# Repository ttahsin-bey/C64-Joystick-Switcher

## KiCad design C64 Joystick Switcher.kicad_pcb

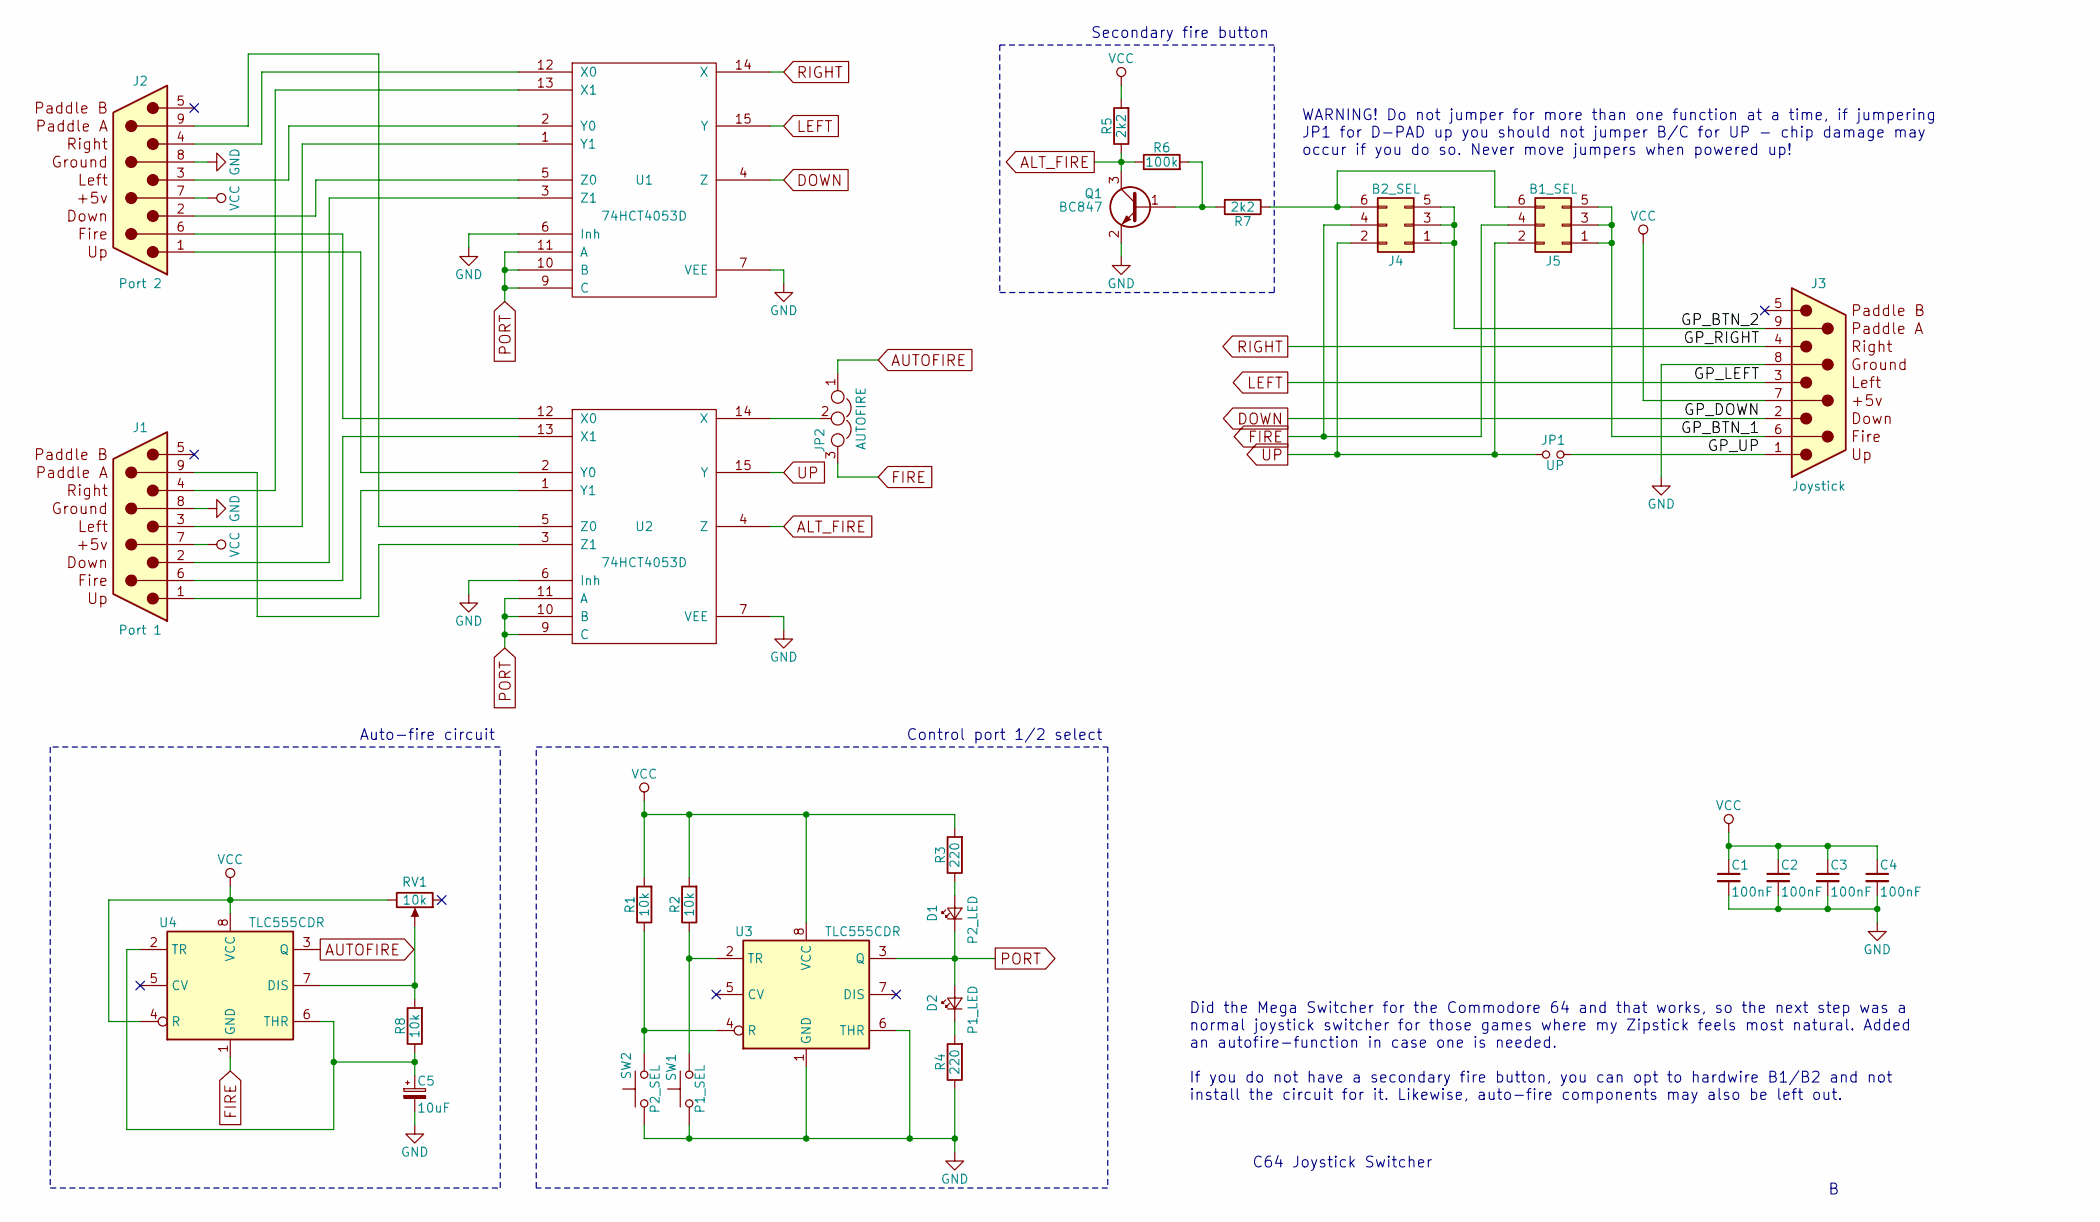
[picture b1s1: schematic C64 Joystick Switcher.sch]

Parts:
C1, C2, C3, C4: 100nF; C_0603_1608Metric; JLCPCB C14663
C5: 10uF; CP_EIA-3216-18_Kemet-A; JLCPCB C7171
D1: P2_LED; LED_0603_1608Metric; JLCPCB C2286
D2: P1_LED; LED_0603_1608Metric; JLCPCB C2286
J1: Port 1; DSUB-9_Female_Horizontal_P2.77x2.84mm_EdgePinOffset7.70mm_H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
J2: Port 2; DSUB-9_Female_Horizontal_P2.77x2.84mm_EdgePinOffset7.70mm_H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
J3: Joystick; DSUB-9_Male_Horizontal_P2.77x2.84mm_EdgePinOffset7.70mm_Hou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
J4: B2_SEL; Pin_Header_Straight_2x03_Pitch2.54mm
J5: B1_SEL; Pin_Header_Straight_2x03_Pitch2.54mm
JP1: UP; Pin_Header_Straight_1x02_Pitch2.54mm
JP2: AUTOFIRE; Pin_Header_Straight_1x03_Pitch2.54mm
Q1: BC847; SOT-23; JLCPCB C57668
R1, R2, R8: 10k; R_0603_1608Metric; JLCPCB C25804
R3, R4: 220; R_0603_1608Metric; JLCPCB C22962
R5, R7: 2k2; R_0603_1608Metric; JLCPCB C4190
R6: 100k; R_0603_1608Metric; JLCPCB C25803
RV1: 10k; Potentiometer_Piher_PT-6-V_Vertical
SW1: P1_SEL; SW_Tactile_SPST_Angled_PTS645Vx58-2LFS
SW2: P2_SEL; SW_Tactile_SPST_Angled_PTS645Vx58-2LFS
U1, U2: 74HCT4053D; SO-16_3.9x9.9mm_P1.27mm; JLCPCB C5996
U3, U4: TLC555CDR; SO-8_3.9x4.9mm_P1.27mm; JLCPCB C6986

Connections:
/GP_BTN_1: J3.6, J5.1, J5.3, J5.5
/GP_BTN_2: J3.9, J4.1, J4.3, J4.5
/GP_UP: J3.1, JP1.2
ALT_FIRE: Q1.3 (C), R5.1, R6.1, U2.4 (Z)
AUTOFIRE: JP2.1, U4.3 (Q)
DOWN: J3.2, U1.4 (Z)
FIRE: J4.4, J5.4, JP2.3, U4.1 (GND)
GND: C1.2, C2.2, C3.2, C4.2, C5.2, J1.8 (GND), J2.8 (GND), J3.8 (GND), Q1.2 (E), R4.1, SW1.2, SW2.1, U1.6 (Inh), U1.7 (VEE), U1.8 (GND), U2.6 (Inh), U2.7 (VEE), U2.8 (GND), U3.1 (GND), U3.6 (THR)
LEFT: J3.3, U1.15 (Y)
unnamed: C5.1, R8.1, U4.2 (TR), U4.6 (THR)
unnamed: D1.2 (A), R3.1
unnamed: D2.1 (K), R4.2
unnamed: J1.1, U2.1 (Y1)
unnamed: J1.2, U1.3 (Z1)
unnamed: J1.3, U1.1 (Y1)
unnamed: J1.4, U1.13 (X1)
unnamed: J1.6, U2.13 (X1)
unnamed: J1.9, U2.3 (Z1)
unnamed: J2.1, U2.2 (Y0)
unnamed: J2.2, U1.5 (Z0)
unnamed: J2.3, U1.2 (Y0)
unnamed: J2.4, U1.12 (X0)
unnamed: J2.6, U2.12 (X0)
unnamed: J2.9, U2.5 (Z0)
unnamed: J4.6, J5.6, R7.1
unnamed: JP2.2, U2.14 (X)
unnamed: Q1.1 (B), R6.2, R7.2
unnamed: R1.1, SW2.2, U3.4 (R)
unnamed: R2.1, SW1.1, U3.2 (TR)
unnamed: R8.2, RV1.2, U4.7 (DIS)
PORT: D1.1 (K), D2.2 (A), U1.9 (C), U1.10 (B), U1.11 (A), U2.9 (C), U2.10 (B), U2.11 (A), U3.3 (Q)
RIGHT: J3.4, U1.14 (X)
UP: J4.2, J5.2, JP1.1, U2.15 (Y)
VCC: C1.1, C2.1, C3.1, C4.1, J1.7 (VCC), J2.7 (VCC), J3.7 (VCC), R1.2, R2.2, R3.2, R5.2, RV1.3, U1.16 (VCC), U2.16 (VCC), U3.8 (VCC), U4.4 (R), U4.8 (VCC)

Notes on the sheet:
C64 Joystick Switcher
WARNING! Do not jumper for more than one function at a time, if jumpering JP1 for D-PAD up you should not jumper B/C for UP - chip damage may occur if you do so. Never move jumpers when powered up!
Did the Mega Switcher for the Commodore 64 and that works, so the next step was a normal joystick switcher for those games where my Zipstick feels most natural. Added an autofire-function in case one is needed. If you do not have a secondary fire button, you can opt to hardwire B1/B2 and not instal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
Auto-fire circuit
Control port 1/2 select
Secondary fire button

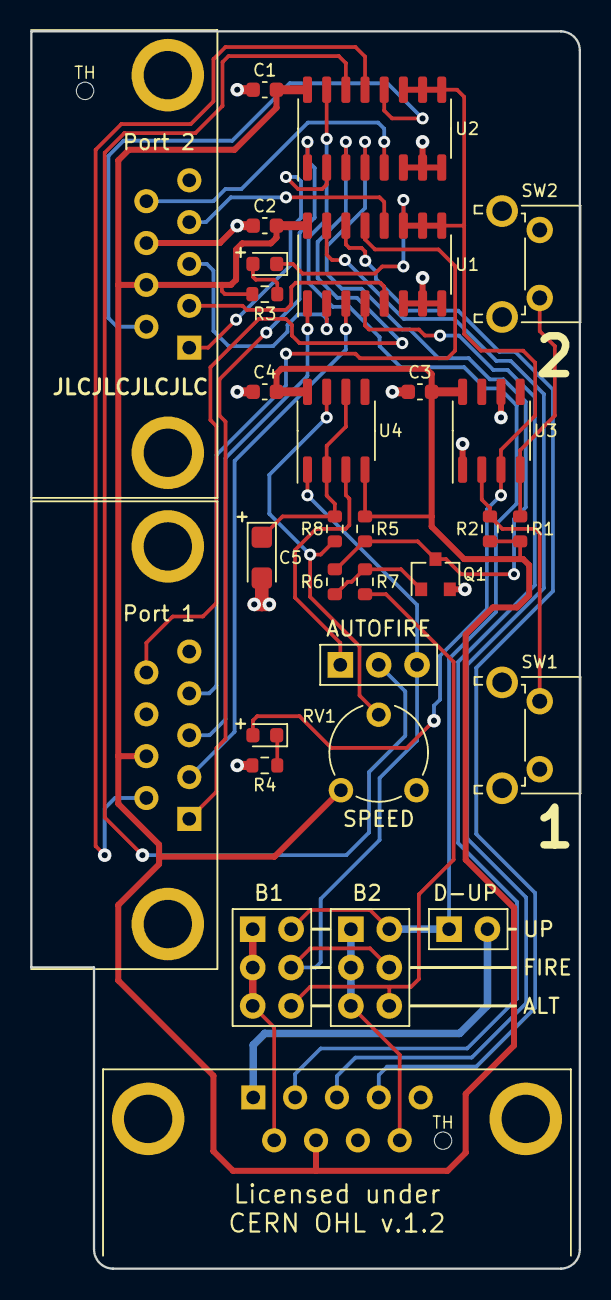
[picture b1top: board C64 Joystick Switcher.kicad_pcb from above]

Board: 2 copper layers, 36.3 x 81.9 mm, 32 parts (0 on the bottom side), 34 nets.

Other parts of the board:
TH: Tooling Hole 1,1mm; MountingHole_2.1mm
TH#2: Tooling Hole 1,1mm; MountingHole_2.1mm

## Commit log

2021-12-19 Layout done. PCB ready for manufacturing.

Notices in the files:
C64 Joystick Switcher.kicad_pcb:
Licensed under
CERN OHL v.1.2
